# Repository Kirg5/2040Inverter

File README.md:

# 2040Inverter
 RP2040 Based BLDC Inverter for sensored motors, capable of putting out 50a 100v, for use in high power ebike/escooter applications.

## Usage
This is a standalone motor inverter, and not a complete motor controller. It does not contain any inputs for assist sensors or throttles as these are sent to the inverter over UART by a seperate MCU, located in the display. You can find the files for the display [here](https://github.com/Kirg5/RP2040-ILI9488-HUD). 

Upon power-up, the fan will breifly be set to full speed, the brake light will turn white, and 6 tones from 1khz to 6khz will be played as part of the self test sequence. If less than 6 tones play it indicates an issue sending power to each of the motor phases and the inverter will throw itself into an error state. Error states can also be thrown if an issue is detected with any of the sensors (current sensor, voltage sensor, either temperature sensor, or motor encoder)

The inverter shall recieve a throttle input from the MCU in the display over uart with a range of 0-255. These values correlate to the current that the inverter will attempt to draw from the battery, ranging from 0 to the maximum set forward current as defined in the firmware. The maximum forward current should never be set higher than 50A with this inverter (30A without active cooling). The throttle does not directly control duty cycle, and instead the duty cycle is controlled through a PID loop that will match the current draw to the requested current. This PID system will work at low speeds, but as the motor EMF approaches the battery voltage at high speeds, the ability to continue to feed current into the motor will fall off. When the PID loop can no longer provide the requested current to the motor (when Dutycycle<sub>PID</sub> > Dutycycle<sub>throttle</sub>), it will smoothly switch to using the direct value from the throttle instead of the PID controlled value.

This inverter supports regenerative braking, where the kinetic energy that would normally be lost to heat while decellerating gets converted into electrical energy to charge the battery. It works in a very similar fashion to the forward power control where a regen signal with a value ranging from 0-255 is sent from the display MCU to the inverter, and it uses a pid loop to map these values to a range of 0 to the maximum reverse current defined in the firmware. The maximum reverse current should be set to the maximum charge current of your BMS, or the maximum charge current of your cells multipled by the number of parallel groups, whichever is lower. You should never set the maximum reverse current value higher than 50a even if your battery can handle it as the current sensor on the inverter cannot measure currents this high, and it can cause damage to the PCB and it's components, especially if you are not using active cooling.

## Wiring 
Wiring the inverter is fairly straightforward; there are 5 large power pads along the top edge and a 16 pin JST connector along the bottom edge, and 2 sets of labelled through holes for the thermistor and the fan.
### The 5 power pads as ordered from left to right are:
1. +VCC (abs. max 100V)
2. GND
3. Phase A (Blue Phase)
4. Phase B (Green Phase)
5. Phase C (Yellow Phase)

### The 16 pins on the JST connector in numerical order are:
1.  LedR    (For brake light, active low)
2.  LedG    (For brake light, active low)
3.  LedB    (For brake light, active low)
4.  RlyCTL  (Output to main relay MOSFET/BJT)
5.  PWR_OK  (Signal from display MCU that precharging has finished and it is ok to power on)
6.  BOOTSEL (RP2040 bootsel button, for firmware flashing)
7.  +12v    (12v 500mA output)
8.  +5v     (5v 500mA output)
9.  USB_DP  (To USB port)
10. USB_DM  (To USB port)
11. UartTX  (To display)
12. UartRX  (To display)
13. HallC   (Blue hall line, active low)
14. HallB   (Green hall line, active low)
15. HallA   (Yellow hall line, active low)
16. GND

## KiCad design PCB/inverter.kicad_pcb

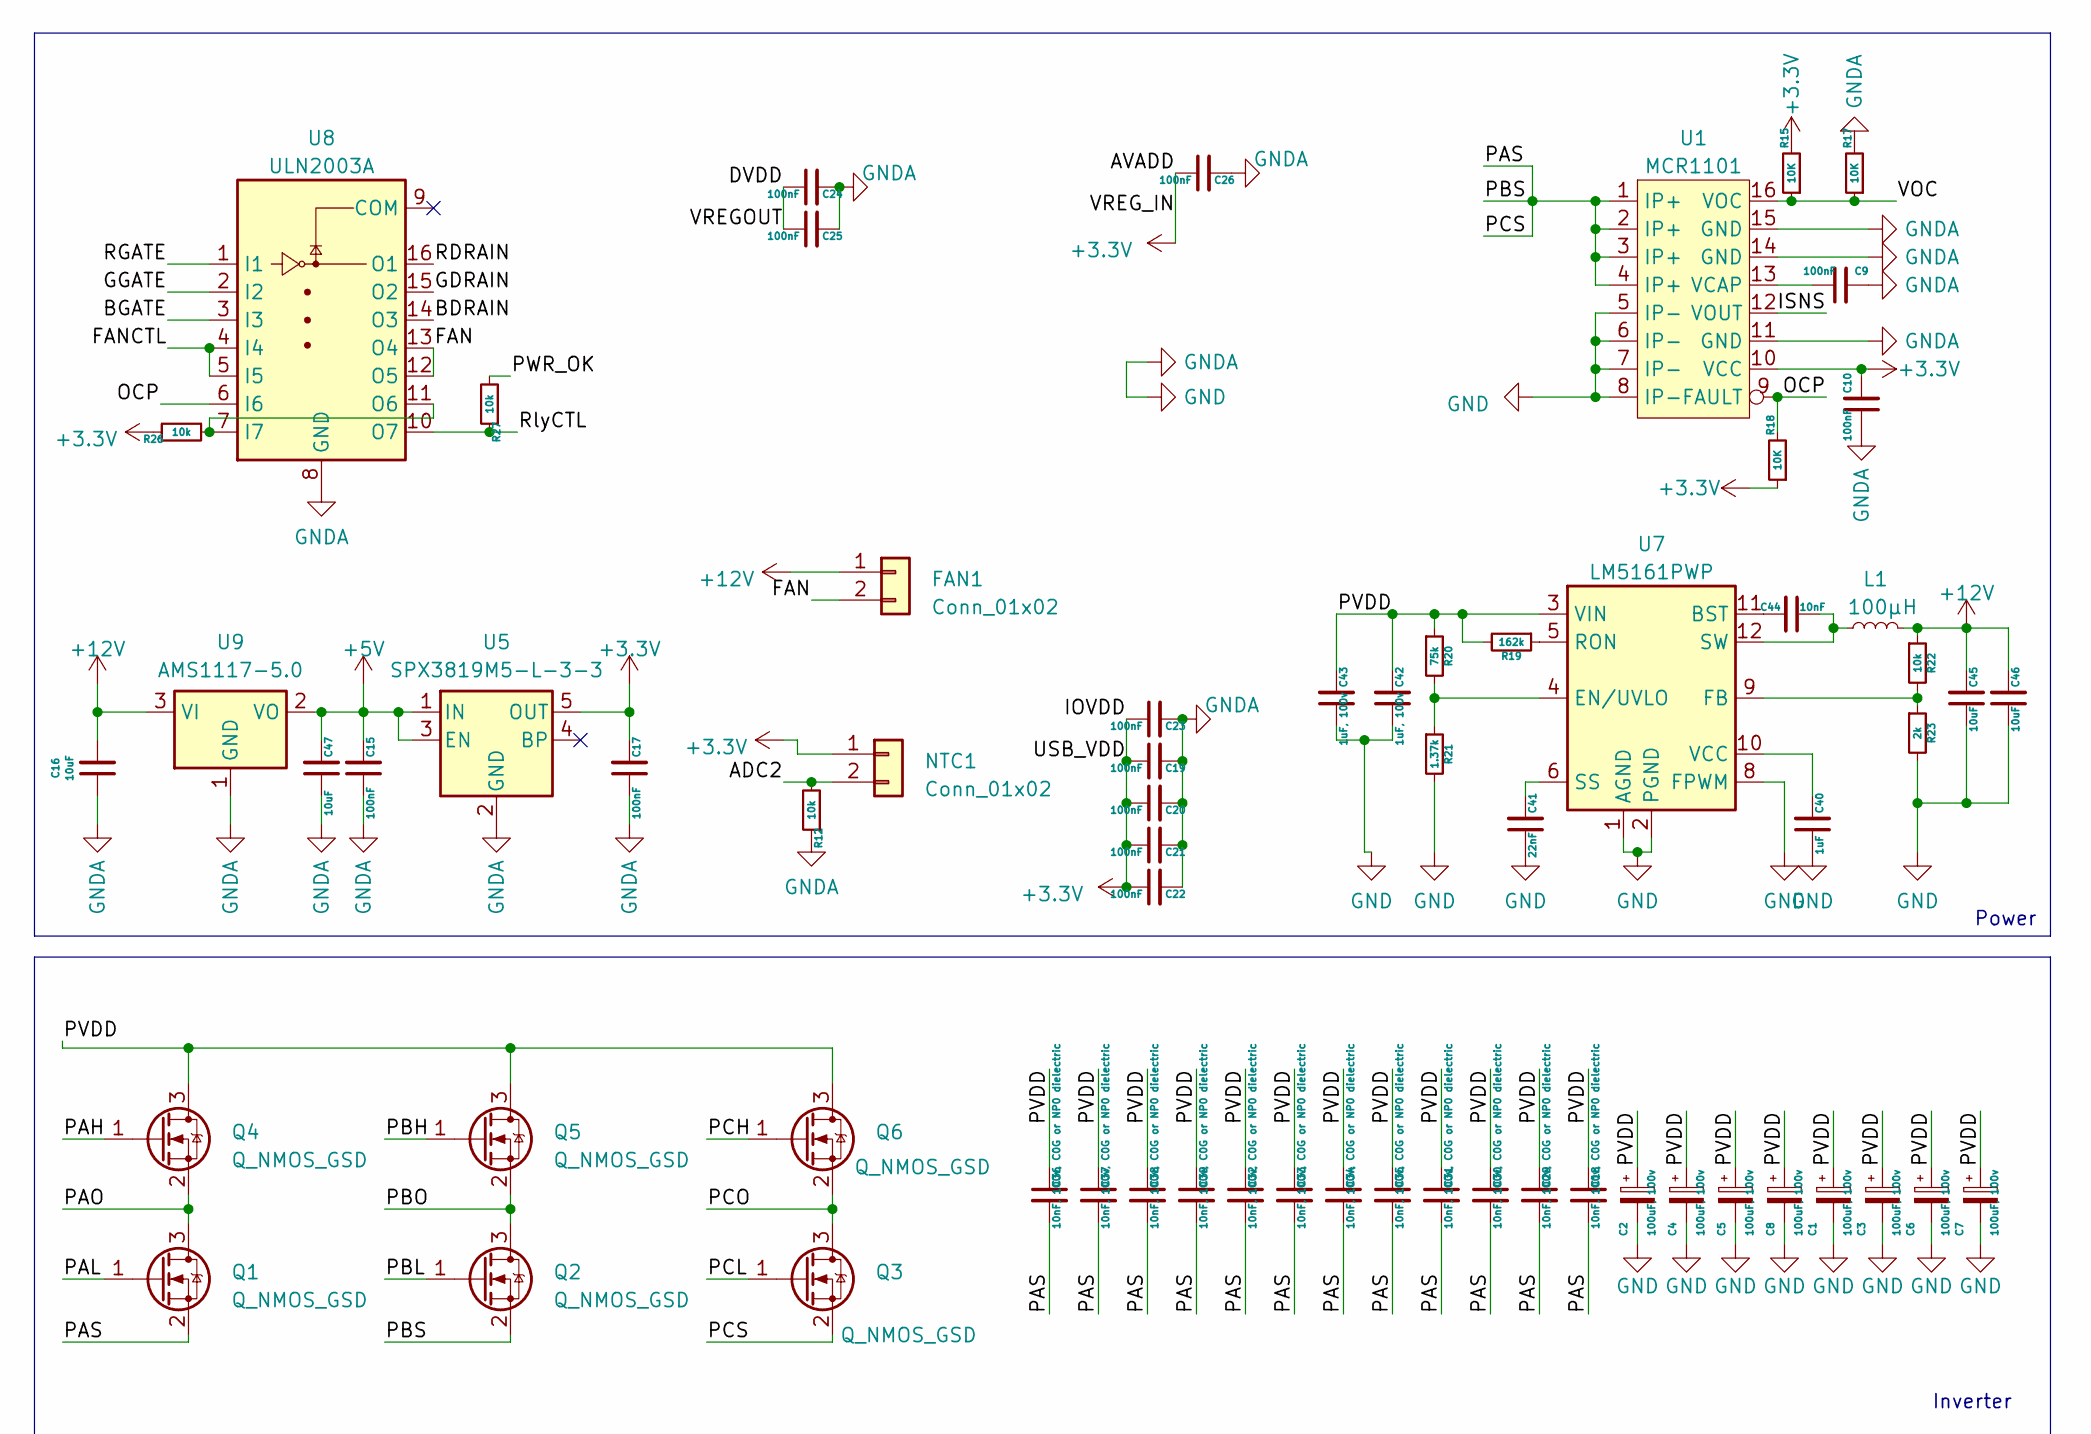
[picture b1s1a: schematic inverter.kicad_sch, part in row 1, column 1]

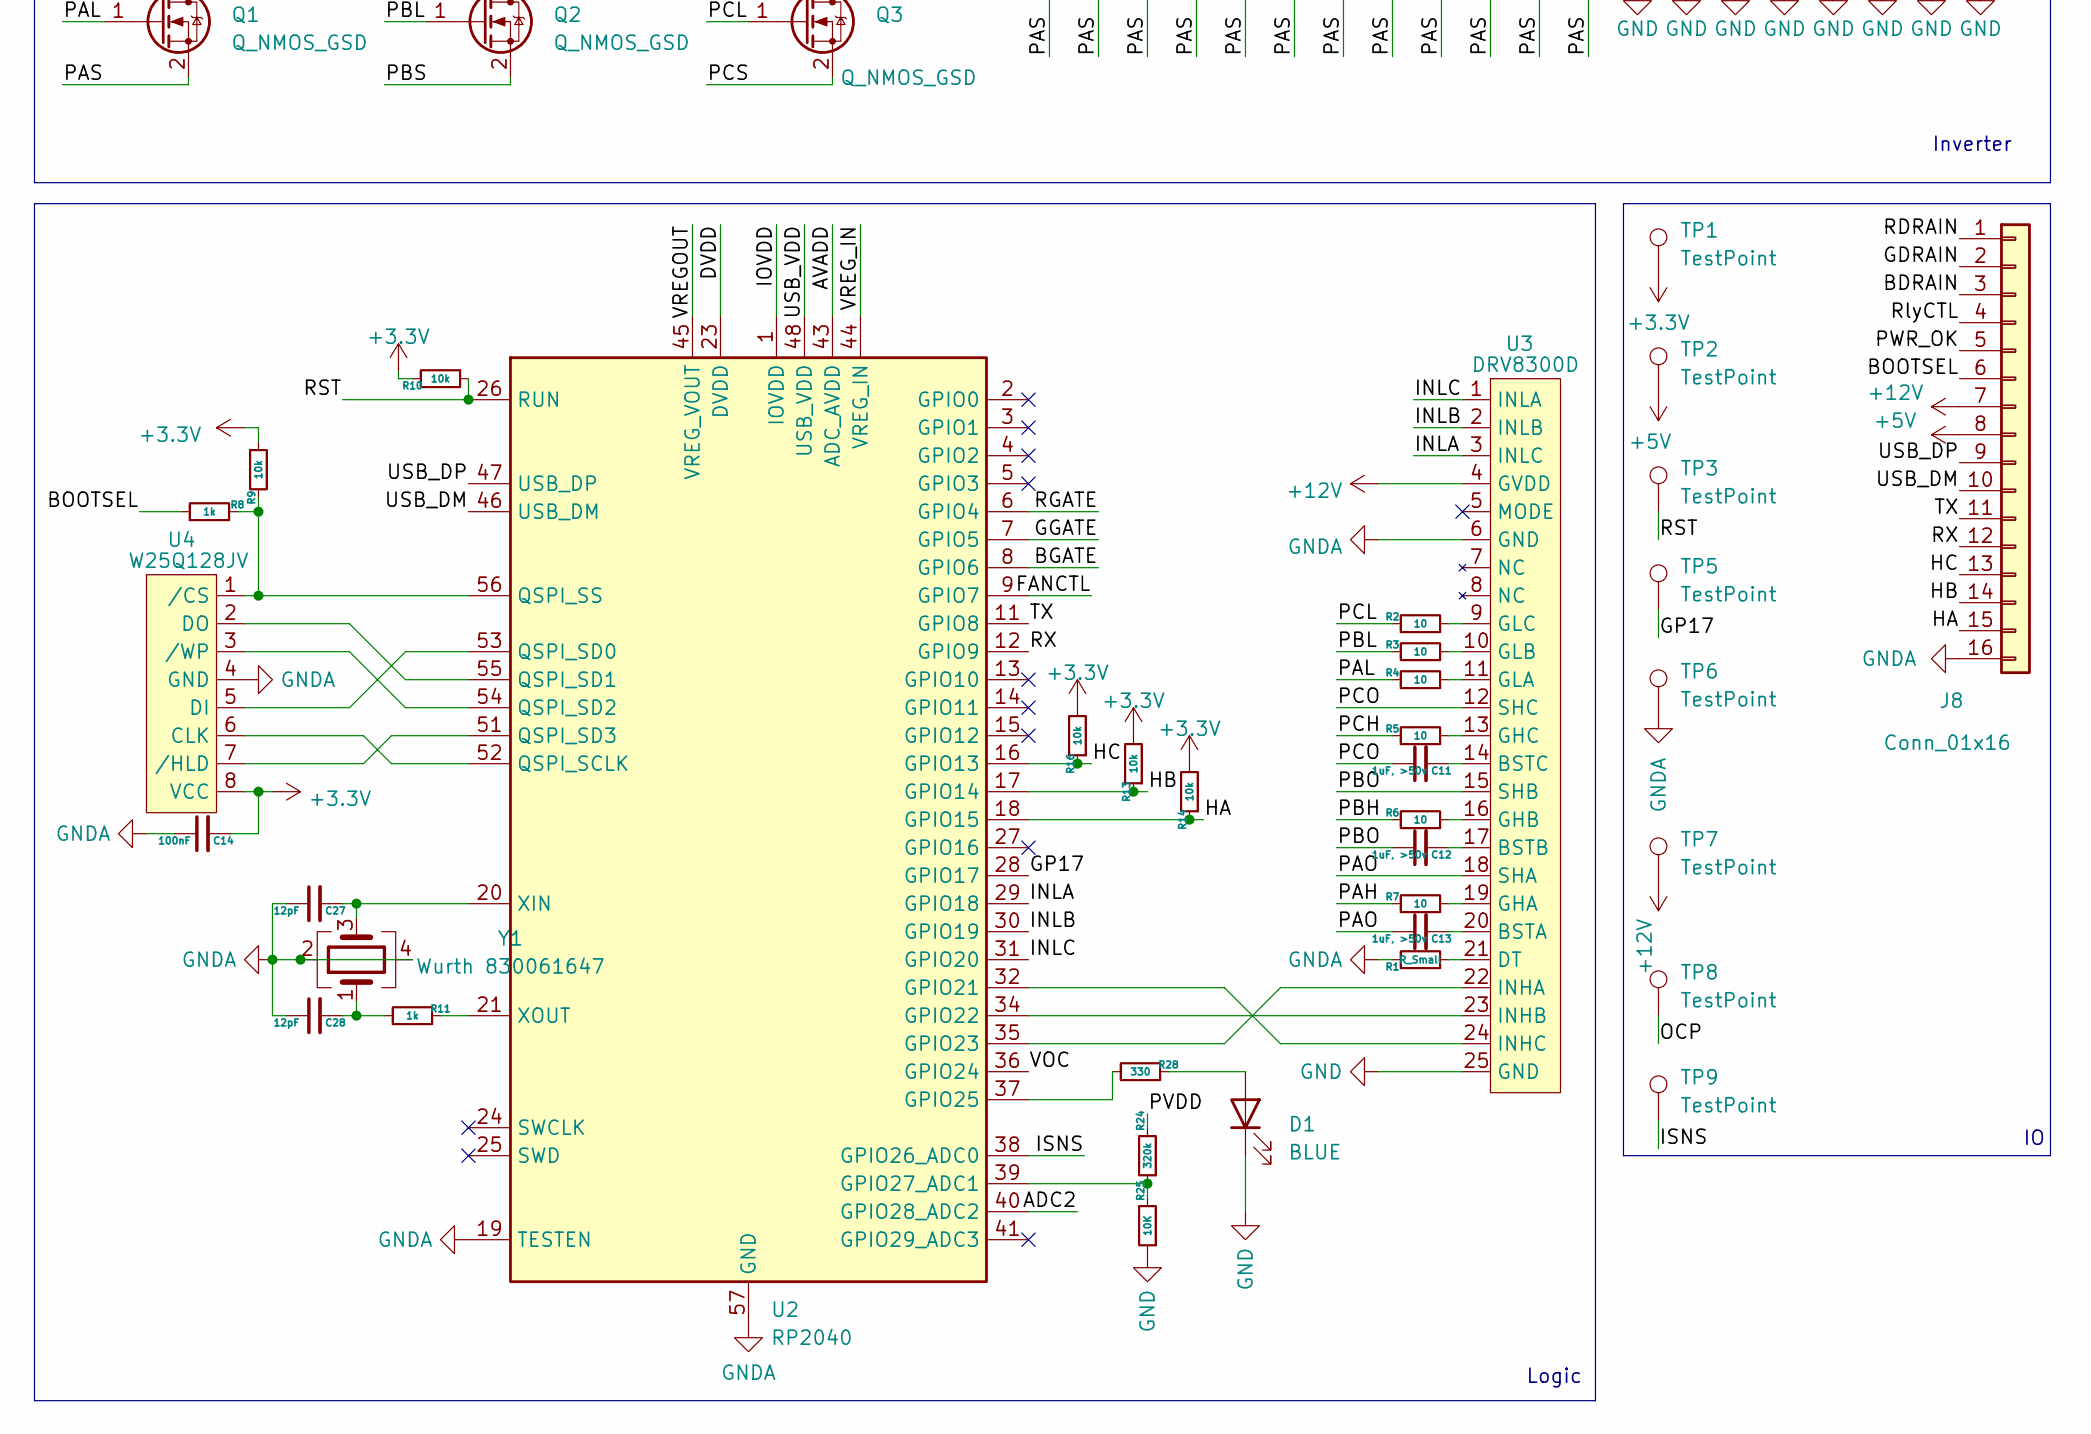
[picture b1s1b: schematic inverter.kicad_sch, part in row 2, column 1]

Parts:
C1, C2, C3, C4, C5, C6, C7, C8: 100uF, 100v; CP_Radial_D8.0mm_P3.50mm
C9, C10, C14, C15, C17, C19, C20, C21, C22, C23, C24, C25, C26: 100nF; C_0402_1005Metric_Pad0.74x0.62mm_HandSolder
C11, C12, C13: 1uF, >50v; C_0603_1608Metric_Pad1.08x0.95mm_HandSolder
C16, C47: 10uF; C_0805_2012Metric_Pad1.18x1.45mm_HandSolder
C18, C29, C30, C31, C32, C33, C34, C35, C36, C37, C38, C39: 10nF, 100v, C0G or NP0 dielectric; C_1206_3216Metric_Pad1.33x1.80mm_HandSolder
C27, C28: 12pF; C_0402_1005Metric_Pad0.74x0.62mm_HandSolder
C40: 1uF; C_0603_1608Metric_Pad1.08x0.95mm_HandSolder
C41: 22nF; C_0603_1608Metric_Pad1.08x0.95mm_HandSolder
C42, C43: 1uF, 100v; C_0805_2012Metric_Pad1.18x1.45mm_HandSolder
C44: 10nF; C_0603_1608Metric_Pad1.08x0.95mm_HandSolder
C45, C46: 10uF; C_1206_3216Metric_Pad1.33x1.80mm_HandSolder
D1: BLUE; LED_0805_2012Metric_Pad1.15x1.40mm_HandSolder
FAN1: Conn_01x02; TestPoint_2Pads_Pitch2.54mm_Drill0.8mm
J8: Conn_01x16; JST_XH_B16B-XH-A_1x16_P2.50mm_Vertical
L1: 100µH; Wurth 74404084560
NTC1: Conn_01x02; TestPoint_2Pads_Pitch2.54mm_Drill0.8mm
Q1, Q2, Q3, Q4, Q5, Q6: Q_NMOS_GSD; Infineon_PG-HSOF-8-1
R1: R_Small; R_0805_2012Metric_Pad1.20x1.40mm_HandSolder
R2, R3, R4, R5, R6, R7: 10; R_0805_2012Metric_Pad1.20x1.40mm_HandSolder
R8, R11: 1k; R_0402_1005Metric_Pad0.72x0.64mm_HandSolder
R9, R10, R12, R22: 10k; R_0402_1005Metric_Pad0.72x0.64mm_HandSolder
R13, R14, R16, R26, R27: 10k; R_0805_2012Metric_Pad1.20x1.40mm_HandSolder
R15, R17, R18, R25: 10K; R_0402_1005Metric_Pad0.72x0.64mm_HandSolder
R19: 162k; R_0402_1005Metric_Pad0.72x0.64mm_HandSolder
R20: 75k; R_0402_1005Metric_Pad0.72x0.64mm_HandSolder
R21: 1.37k; R_0402_1005Metric_Pad0.72x0.64mm_HandSolder
R23: 2k; R_0402_1005Metric_Pad0.72x0.64mm_HandSolder
R24: 320k; R_0402_1005Metric_Pad0.72x0.64mm_HandSolder
R28: 330; R_0402_1005Metric_Pad0.72x0.64mm_HandSolder
TP1, TP2, TP3, TP5, TP6, TP7, TP8, TP9: TestPoint; TestPoint_Pad_1.5x1.5mm
U1: MCR1101; SOIC-16W_7.5x10.3mm_P1.27mm
U2: RP2040; QFN-56-1EP_7x7mm_P0.4mm_EP3.2x3.2mm
U3: DRV8300D; VQFN-24-1EP_4x4mm_P0.5mm_EP2.5x2.5mm
U4: W25Q128JV; SOIC-8-1EP_3.9x4.9mm_P1.27mm_EP2.29x3mm
U5: SPX3819M5-L-3-3; SOT-23-5
U7: LM5161PWP; HTSSOP-14-1EP_4.4x5mm_P0.65mm_EP3.4x5mm_Mask3x3.1mm
U8: ULN2003A; SOIC-16_3.9x9.9mm_P1.27mm
U9: AMS1117-5.0; SOT-223-3_TabPin2
Y1: Wurth 830061647; Crystal_SMD_3225-4Pin_3.2x2.5mm_HandSoldering

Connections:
+3.3V: C10.2, C14.2, C17.2, C19.1, C20.1, C21.1, C22.1, C23.1, C26.1, NTC1.1, R9.1, R10.2, R13.2, R14.2, R15.2, R16.2, R18.1, R26.1, TP1.1, U1.10 (VCC), U2.1 (IOVDD), U2.10 (IOVDD), U2.22 (IOVDD), U2.33 (IOVDD), U2.42 (IOVDD), U2.43 (ADC_AVDD), U2.44 (VREG_IN), U2.48 (USB_VDD), U2.49 (IOVDD), U4.8 (VCC), U5.5 (OUT); also elsewhere on the board
+5V: C15.2, C47.2, J8.8, TP2.1, U5.1 (IN), U5.3 (EN), U9.2 (VO)
+12V: C16.2, C45.2, C46.2, FAN1.1, J8.7, L1.2, R22.1, TP7.1, U3.4 (GVDD), U9.3 (VI); also elsewhere on the board
/ADC2: NTC1.2, R12.2, U2.40 (GPIO28_ADC2); also elsewhere on the board
/BDRAIN: J8.3, U8.14 (O3)
/BGATE: U2.8 (GPIO6), U8.3 (I3)
/BOOTSEL: J8.6, R8.1
/DVDD: C24.1, C25.1, U2.23 (DVDD), U2.45 (VREG_VOUT), U2.50 (DVDD)
/FAN: FAN1.2, U8.12 (O5), U8.13 (O4); also elsewhere on the board
/FANCTL: U2.9 (GPIO7), U8.4 (I4), U8.5 (I5)
/GDRAIN: J8.2, U8.15 (O2)
/GGATE: U2.7 (GPIO5), U8.2 (I2)
/GP17: TP5.1, U2.28 (GPIO17)
/HA: J8.15, R14.1, U2.18 (GPIO15)
/HB: J8.14, R13.1, U2.17 (GPIO14)
/HC: J8.13, R16.1, U2.16 (GPIO13)
/INLA: U2.29 (GPIO18), U3.3 (INLC)
/INLB: U2.30 (GPIO19), U3.2 (INLB)
/INLC: U2.31 (GPIO20), U3.1 (INLA)
/ISNS: TP9.1, U1.12 (VOUT), U2.38 (GPIO26_ADC0)
/OCP: R18.2, TP8.1, U1.9 (FAULT), U8.6 (I6)
/PAH: Q4.1 (G), R7.1
/PAL: Q1.1 (G), R4.1
/PAO: C13.1, Q1.3 (D), Q4.2 (S), U3.18 (SHA)
/PAS: C18.2, C29.2, C30.2, C31.2, C32.2, C33.2, C34.2, C35.2, C36.2, C37.2, C38.2, C39.2, Q1.2 (S), Q2.2 (S), Q3.2 (S), U1.1 (IP+), U1.2 (IP+), U1.3 (IP+), U1.4 (IP+)
/PBH: Q5.1 (G), R6.1
/PBL: Q2.1 (G), R3.1
/PBO: C12.1, Q2.3 (D), Q5.2 (S), U3.15 (SHB)
/PCH: Q6.1 (G), R5.1
/PCL: Q3.1 (G), R2.1
/PCO: C11.1, Q3.3 (D), Q6.2 (S), U3.12 (SHC)
/PVDD: C1.1, C2.1, C3.1, C4.1, C5.1, C6.1, C7.1, C8.1, C18.1, C29.1, C30.1, C31.1, C32.1, C33.1, C34.1, C35.1, C36.1, C37.1, C38.1, C39.1, C42.2, C43.2, Q4.3 (D), Q5.3 (D), Q6.3 (D), R19.2, R20.1, R24.2, U7.3 (VIN)
/PWR_OK: J8.5, R27.2
/RDRAIN: J8.1, U8.16 (O1)
/RGATE: U2.6 (GPIO4), U8.1 (I1)
/RST: R10.1, TP3.1, U2.26 (RUN)
/RX: J8.12, U2.12 (GPIO9)
/RlyCTL: J8.4, R27.1, U8.10 (O7)
/TX: J8.11, U2.11 (GPIO8)
/USB_DM: J8.10, U2.46 (USB_DM)
/USB_DP: J8.9, U2.47 (USB_DP)
/VOC: R15.1, R17.1, U1.16 (VOC), U2.36 (GPIO24)
GND: C1.2, C2.2, C3.2, C4.2, C5.2, C6.2, C7.2, C8.2, C9.2, C10.1, C14.1, C15.1, C16.1, C17.1, C19.2, C20.2, C21.2, C22.2, C23.2, C24.2, C25.2, C26.2, C27.1, C28.1, C40.1, C41.1, C42.1, C43.1, C45.1, C46.1, C47.1, D1.1 (K), J8.16, R1.1, R12.1, R17.2, R21.2, R23.2, R25.1, TP6.1, U1.5 (IP-), U1.6 (IP-), U1.7 (IP-), U1.8 (IP-), U1.11 (GND), U1.14 (GND), U1.15 (GND), U2.19 (TESTEN), U2.57 (GND), U3.6 (GND), U3.25 (GND), U4.4 (GND), U5.2 (GND), U7.1 (AGND), U7.2 (PGND), U7.8 (FPWM), U7.15 (AGND), U8.8 (GND), U9.1 (GND), Y1.2, Y1.4
unnamed: C28.2, R11.1, Y1.1
unnamed: C44.1, L1.1, U7.12 (SW), U7.13 (SW)
unnamed: D1.2 (A), R28.1
unnamed: C9.1, U1.13 (VCAP)
unnamed: U2.32 (GPIO21), U3.24 (INHC)
unnamed: U2.34 (GPIO22), U3.23 (INHB)
unnamed: U2.35 (GPIO23), U3.22 (INHA)
unnamed: R28.2, U2.37 (GPIO25)
unnamed: R24.1, R25.2, U2.39 (GPIO27_ADC1)
unnamed: U2.52 (QSPI_SCLK), U4.6 (CLK)
unnamed: U2.53 (QSPI_SD0), U4.5 (DI)
unnamed: U2.55 (QSPI_SD1), U4.2 (DO)
unnamed: U2.54 (QSPI_SD2), U4.3 (/WP)
unnamed: U2.51 (QSPI_SD3), U4.7 (/HLD)
unnamed: R8.2, R9.2, U2.56 (QSPI_SS), U4.1 (/CS)
unnamed: C27.2, U2.20 (XIN), Y1.3
unnamed: R11.2, U2.21 (XOUT)
unnamed: C13.2, U3.20 (BSTA)
unnamed: C12.2, U3.17 (BSTB)
unnamed: C11.2, U3.14 (BSTC)
unnamed: R1.2, U3.21 (DT)
unnamed: R7.2, U3.19 (GHA)
unnamed: R6.2, U3.16 (GHB)
unnamed: R5.2, U3.13 (GHC)
unnamed: R4.2, U3.11 (GLA)
unnamed: R3.2, U3.10 (GLB)
unnamed: R2.2, U3.9 (GLC)
unnamed: C44.2, U7.11 (BST)
unnamed: R20.2, R21.1, U7.4 (EN/UVLO)
unnamed: R22.2, R23.1, U7.9 (FB)
unnamed: R19.1, U7.5 (RON)
unnamed: C41.2, U7.6 (SS)
unnamed: C40.2, U7.10 (VCC)
unnamed: R26.2, U8.7 (I7), U8.11 (O6)

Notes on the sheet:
Inverter
Power
Logic

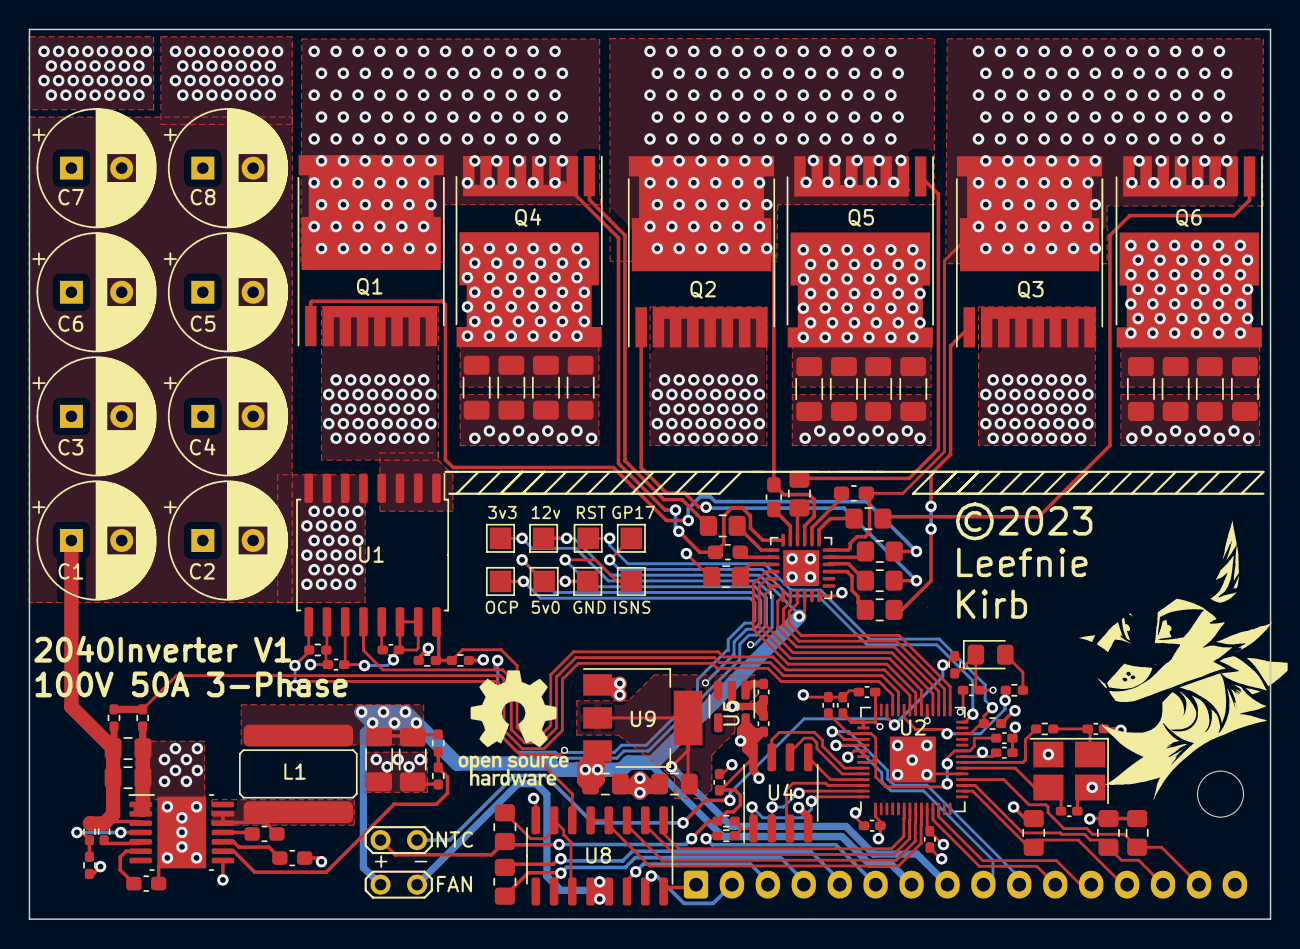
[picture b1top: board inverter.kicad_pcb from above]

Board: 4 copper layers, 86.4 x 61.9 mm, 103 parts (1 on the bottom side), 77 nets.

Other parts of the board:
FAN: Conn_01x02; TestPoint_2Pads_Pitch2.54mm_Drill0.8mm
NTC: Conn_01x02; TestPoint_2Pads_Pitch2.54mm_Drill0.8mm

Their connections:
+3.3V: NTC.1; also elsewhere on the board
+12V: FAN.1; also elsewhere on the board
/ADC2: NTC.2; also elsewhere on the board
/FAN: FAN.2; also elsewhere on the board

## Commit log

2023-08-11 Create repository
2023-10-21 Fix incorrect PWM frequency
2023-10-22 Better sine LUT
2023-10-22 rearranged variables and added speed calculations
2023-11-18 Fix incorrect low side pin numbers
2023-11-18 comment out parts of code for testing
2023-11-18 Add self-test mode
2023-11-19 add image source to readme
2023-11-19 comment define variables
2023-11-20 Update README.md
    Fix incorrect hall sensor wiring
2023-12-19 Implement wheel speed sensing and adaptive PWM frequency

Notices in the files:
PCB/inverter.kicad_pcb:
©️2023
